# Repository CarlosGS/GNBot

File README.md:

GNBot: robotic platform for cooperative search strategies
=====

Low-cost 3D-printable robot design for testing cooperative search algorithms.  

**Check [the GNBot wiki page](https://github.com/carlosgs/GNBot/wiki) for more information**  

The GNBot design allows the construction of a swarm of remotely-controlled robots that have multimodal sensory input (perceiving light, distance, temperature, humidity and orientation with an electronic compass) and are capable of detecting odor sources such as the low-profile target shown on the left.  

**Demonstration video of the swarm of GNBots used for Lévy-walk-based search:**

These robots are also energy efficient, open-source and easy to expand to allow the implementation of a great variety of cooperative search strategies (including those that use range information from each sensor modality with a characterization of the uncertainty of odor sources, and also the ones that use classical heuristic or brute-force approaches for search). Most importantly, the standardization of the platform could finally provide a fair base of comparison for evaluating differences in efficiency among these odor search strategies.  

List of sensors present in the robot:
TGS-2600 odor sensor, IR rangefinder, LDR light sensor array, electronic compass module, temperature and humidity sensors.
Battery voltage is also monitored.
The base actuators are two servomotors and the wireless interface is based on a ZigBee-compatible module.  

**Version 1.0:**  

Items shown in the picture:
**1)** GNBoard electronics.
**2)** Arduino MEGA board.
**3)** TGS-2600 odor sensor.
**4)** ZigBee-compatible RF module.
**5)** Infra-red distance sensor.
**6)** DHT11 temperature and humidity sensor.
**7)** HMC5883L magnetometer sensor.
**8)** Piezoelectric buzzer.
**9)** Visual marker attachment.
**10)** Two 9V battery connectors.
**11)** Two 9V rechargeable batteries (300mAh).
**12)** Two continuous-rotation servomotors.
**13)** 3D-printed robot wheels.
**14)** Rubber outer-wheel rings.
**15)** 3D-printed GNBot chassis.
**16)** Marble for the idler wheel.  

**Version 1.0a:**  

**Version 0.5:**  

License  
--
License: **Attribution - Share Alike - Creative Commons (<http://creativecommons.org/licenses/by-sa/3.0/>)**  

Author:  
--
**@CarlosGS** <https://github.com/CarlosGS>

Disclaimer  
--
This hardware/software is provided "as is", and you use the hardware/software at your own risk. Under nocircumstances shall any author be liable for direct, indirect, special, incidental, or consequential damages resulting from the use, misuse, or inability to use this hardware/software, even if the authors have been advised of the possibility of such damages.

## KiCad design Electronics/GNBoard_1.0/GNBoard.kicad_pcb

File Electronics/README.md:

Electronics for the GNBot
=====

GNBoard shield for the Arduino MEGA  
--

An efficient solution for powering mobile robots. The GNBoard can also incorporate a ZigBee-compatible module and many other multimodal sensors (a gas detector for odor sensing, an accelerometer/electronic compass, temperature and humidity sensors, luminosity sensors), and multiple kinds of actuators as well (servomotors, a speaker, LEDs, etc).

The two versions of the GNBoard developed for this project.
Prototype design (left) and version 1.0 (right).
The boards are designed to plug into an **Arduino MEGA**.  

The motion of the robot is achieved using two continuous rotation servomotors (**SM-S4303R**) as the main actuators. Servomotors provide a compact and low-cost solution to achieve the digital speed control needed.
The main downside of this kind of actuator is the high current demand -particularly during transient motions- which requires the use of an adequate power supply. For the GNBoard the design decision was to use a switching power supply rather than a linear regulator, provided the much higher efficiency.

**Power supply schematic and actual assembly**
**A)** and **B)** respectively show the power supplies in GNBoard v0.1 and v1.0 (final version).
The power supply of the GNBoard uses an **LM2576-5** switching regulator that is capable of delivering up to 3A, which is more than sufficient to cover the energy demand of the entire robot.
Switching power regulators also have a broad input voltage range, allowing to make better use of the full capacity of the batteries since they can be connected in series without negative effect in the performance.

**Polarization scheme for the artificial nose sensor and detail picture of the assembly:**
The mounted sensor is the **TGS-2600** gas detector from <http://www.figarosensor.com/>, but any kind of sensor with a similar polarization scheme (as shown in the left panel) could be used.

Layout and schematics  

License  
--
License: **Attribution - Share Alike - Creative Commons (<http://creativecommons.org/licenses/by-sa/3.0/>)**  

Author:  
--
**Carlosgs (<http://carlosgs.es>)**  

Disclaimer  
--
This hardware/software is provided "as is", and you use the hardware/software at your own risk. Under nocircumstances shall any author be liable for direct, indirect, special, incidental, or consequential damages resulting from the use, misuse, or inability to use this hardware/software, even if the authors have been advised of the possibility of such damages.

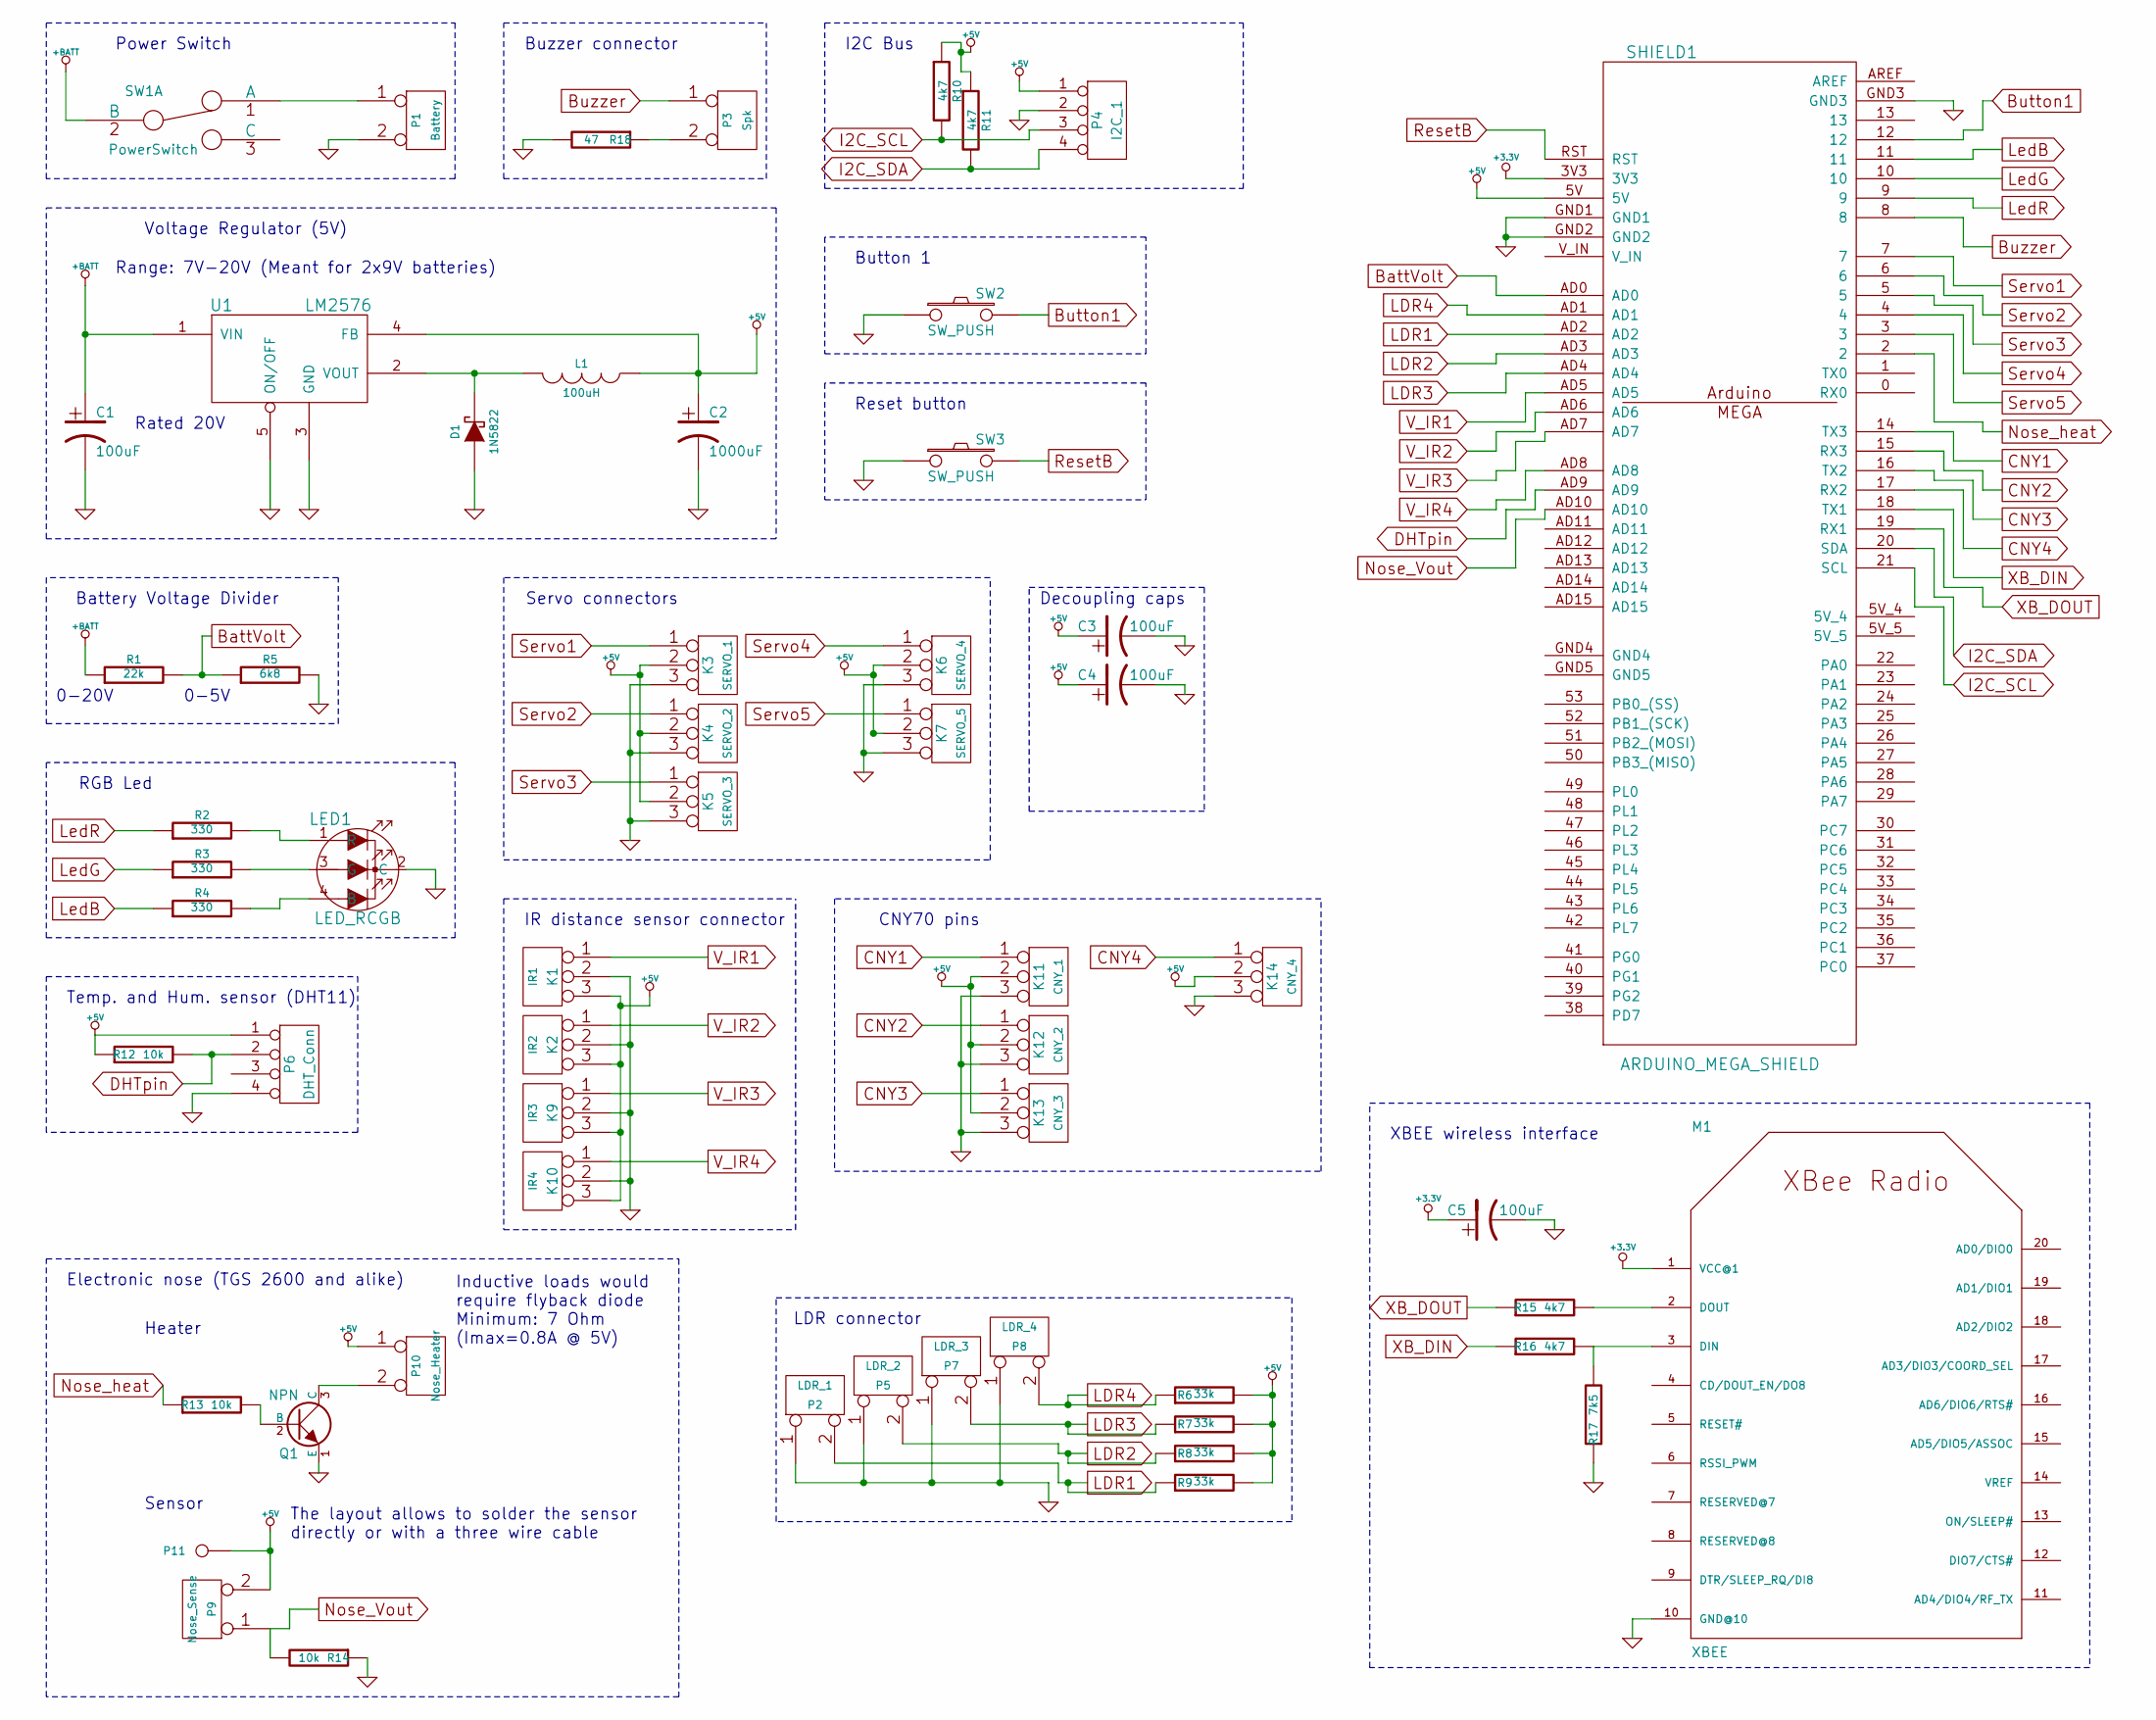
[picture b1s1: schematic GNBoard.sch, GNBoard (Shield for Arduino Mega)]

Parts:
C1, C3, C4, C5: 100uF
C2: 1000uF
D1: 1N5822
K1: IR1
K2: IR2
K3: SERVO_1
K4: SERVO_2
K5: SERVO_3
K6: SERVO_4
K7: SERVO_5
K9: IR3
K10: IR4
K11: CNY_1
K12: CNY_2
K13: CNY_3
K14: CNY_4
L1: 100uH
LED1: LED_RCGB
M1: XBEE; xbee_r1-XBEE
P1: Battery
P2: LDR_1
P3: Spk
P4: I2C_1
P5: LDR_2
P6: DHT_Conn
P7: LDR_3
P8: LDR_4
P9: Nose_Sense
P10: Nose_Heater
P11: CONN_1
Q1: NPN
R1: 22k
R2, R3, R4: 330
R5: 6k8
R6, R7, R8, R9: 33k
R10, R11, R15, R16: 4k7
R12, R13, R14: 10k
R17: 7k5
R18: 47
SHIELD1: ARDUINO_MEGA_SHIELD
SW1: PowerSwitch
SW2, SW3: SW_PUSH
U1: LM2576

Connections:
+3.3V: C5.1, M1.1 (VCC@1), SHIELD1.3V3
+5V: C2.1, C3.1, C4.1, K1.3, K2.3, K3.2 (PM), K4.2 (PM), K5.2 (PM), K6.2 (PM), K7.2 (PM), K9.3, K10.3, K11.2 (PM), K12.2 (PM), K13.2 (PM), K14.2 (PM), L1.1, P4.1, P6.1, P9.2 (PM), P10.1, P11.1, R6.2, R7.2, R8.2, R9.2, R10.1, R11.1, R12.1, SHIELD1.5V, U1.4 (FB)
+BATT: C1.1, R1.1, SW1.2 (B), U1.1 (VIN)
BattVolt: R1.2, R5.1, SHIELD1.AD0
Button1: SHIELD1.12, SW2.2
Buzzer: P3.1, SHIELD1.8
CNY1: K11.1, SHIELD1.14 (TX3)
CNY2: K12.1, SHIELD1.15 (RX3)
CNY3: K13.1, SHIELD1.16 (TX2)
CNY4: K14.1, SHIELD1.17 (RX2)
DHTpin: P6.2, R12.2, SHIELD1.AD9
GND: C1.2, C2.2, C3.2, C4.2, C5.2, D1.1 (A), K1.2 (PM), K2.2 (PM), K3.3, K4.3, K5.3, K6.3, K7.3, K9.2 (PM), K10.2 (PM), K11.3, K12.3, K13.3, K14.3, LED1.2 (C), M1.10 (GND@10), P1.2 (PM), P2.1, P4.2, P5.1, P6.4, P7.1, P8.1, Q1.1 (E), R5.2, R14.1, R17.1, R18.2, SHIELD1.GND1, SHIELD1.GND2, SHIELD1.GND3, SW2.1, SW3.1, U1.3 (GND), U1.5 (ON/OFF)
I2C_SCL: P4.3, R10.2, SHIELD1.21 (SCL)
I2C_SDA: P4.4, R11.2, SHIELD1.20 (SDA)
LDR1: P2.2 (PM), R9.1, SHIELD1.AD2
LDR2: P5.2 (PM), R8.1, SHIELD1.AD3
LDR3: P7.2 (PM), R7.1, SHIELD1.AD4
LDR4: P8.2 (PM), R6.1, SHIELD1.AD1
LedB: R4.1, SHIELD1.11
LedG: R3.1, SHIELD1.10
LedR: R2.1, SHIELD1.9
unnamed: LED1.3 (G), R3.2
unnamed: P3.2 (PM), R18.1
unnamed: LED1.4 (B), R4.2
unnamed: LED1.1 (R), R2.2
unnamed: D1.2 (K), L1.2, U1.2 (VOUT)
unnamed: P1.1, SW1.1 (A)
unnamed: M1.3 (DIN), R16.2, R17.2
unnamed: M1.2 (DOUT), R15.2
unnamed: Q1.2 (B), R13.2
unnamed: P10.2 (PM), Q1.3 (C)
Nose_Vout: P9.1, R14.2, SHIELD1.AD10
Nose_heat: R13.1, SHIELD1.2
ResetB: SHIELD1.RST, SW3.2
Servo1: K3.1, SHIELD1.7
Servo2: K4.1, SHIELD1.6
Servo3: K5.1, SHIELD1.5
Servo4: K6.1, SHIELD1.4
Servo5: K7.1, SHIELD1.3
V_IR1: K1.1, SHIELD1.AD5
V_IR2: K2.1, SHIELD1.AD6
V_IR3: K9.1, SHIELD1.AD7
V_IR4: K10.1, SHIELD1.AD8
XB_DIN: R16.1, SHIELD1.18 (TX1)
XB_DOUT: R15.1, SHIELD1.19 (RX1)

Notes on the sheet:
Voltage Regulator (5V)
RGB Led
Battery Voltage Divider
Power Switch
LDR connector
IR distance sensor connector
Servo connectors
CNY70 pins
Buzzer connector
Reset button
I2C Bus
Button 1
Temp. and Hum. sensor (DHT11)
Decoupling caps
Range: 7V-20V (Meant for 2x9V batteries)
Rated 20V
0-5V
0-20V
Electronic nose (TGS 2600 and alike)
XBEE wireless interface
Inductive loads would require flyback diode Minimum: 7 Ohm (Imax=0.8A @ 5V)
Heater
Sensor
The layout allows to solder the sensor directly or with a three wire cable

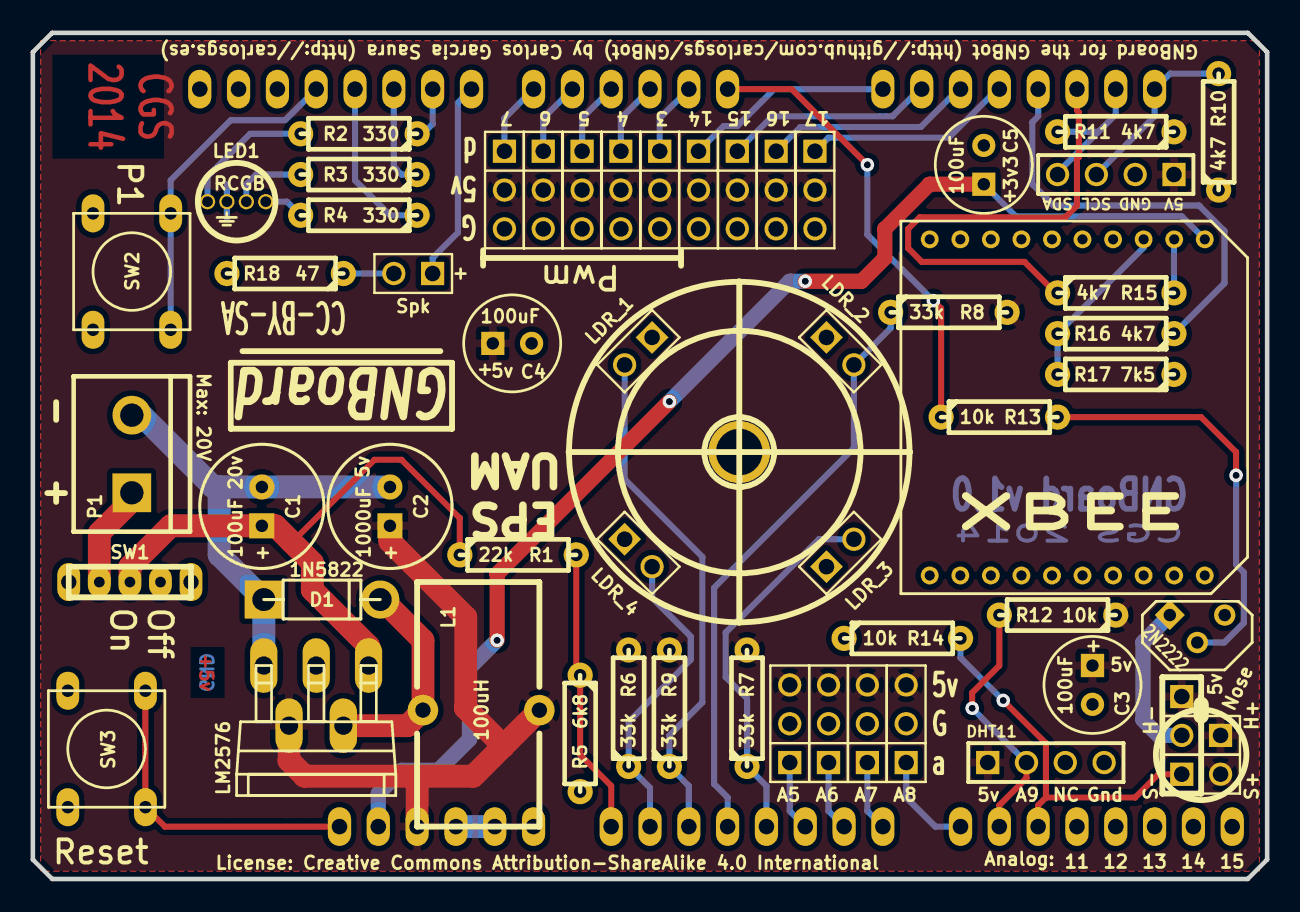
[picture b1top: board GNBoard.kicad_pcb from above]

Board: 2 copper layers, 80.8 x 55.4 mm, 58 parts (0 on the bottom side), 45 nets.

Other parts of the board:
1PIN: P***; ldr_drill

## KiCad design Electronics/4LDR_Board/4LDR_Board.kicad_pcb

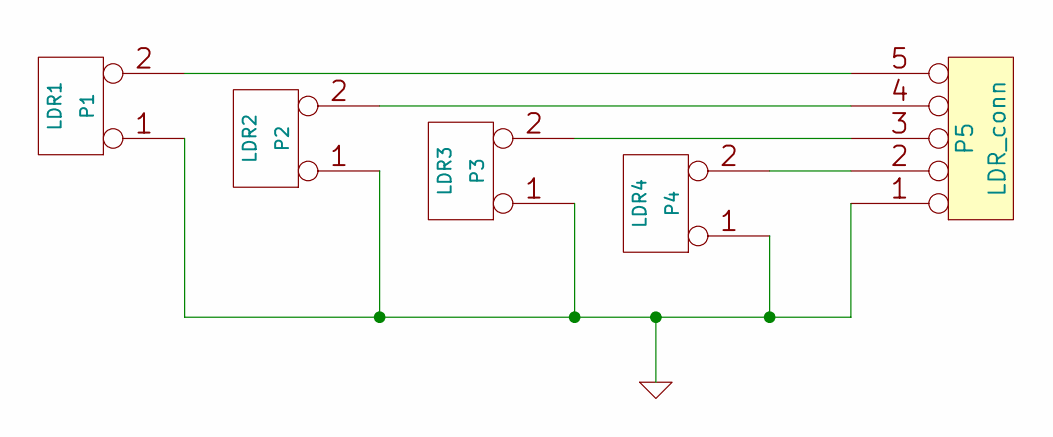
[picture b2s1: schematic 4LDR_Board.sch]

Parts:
P1: LDR1
P2: LDR2
P3: LDR3
P4: LDR4
P5: LDR_conn

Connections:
GND: P1.1, P2.1, P3.1, P4.1, P5.1
unnamed: P2.2 (PM), P5.4
unnamed: P1.2 (PM), P5.5
unnamed: P3.2 (PM), P5.3
unnamed: P4.2 (PM), P5.2

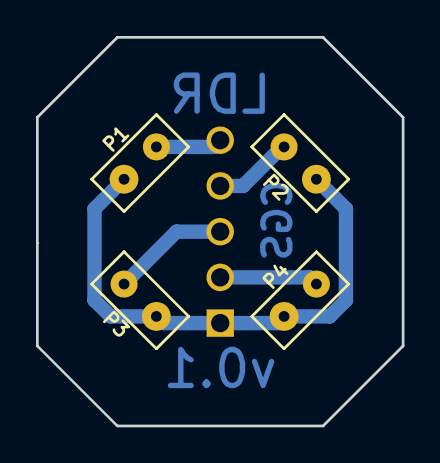
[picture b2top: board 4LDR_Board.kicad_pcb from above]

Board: 2 copper layers, 20.3 x 21.6 mm, 5 parts (1 on the bottom side), 5 nets.

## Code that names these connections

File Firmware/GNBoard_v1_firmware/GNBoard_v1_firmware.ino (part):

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
#define Serial Serial

#define NOSE_HEAT_PIN 2
#define NOSE_VOUT_PIN A10

#define LDR1_PIN A2
#define LDR2_PIN A3
#define LDR3_PIN A4
#define LDR4_PIN A1

#define IR1_PIN A5
#define IR2_PIN A6
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
#define DHT_PIN A9

#define BUZZER_PIN 8

#define SERVO_1_PIN 7
#define SERVO_2_PIN 6
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void playNote(int frequency, int length) {
  if(frequency <= 0) frequency = DO;
  if(length <= 0) length = 100;
  tone(BUZZER_PIN,frequency);
  delay(length);
  noTone(BUZZER_PIN);
  delay(100);
}

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  
  setupMagnetometer();
  
  Servo1.attach(SERVO_1_PIN);
  Servo2.attach(SERVO_2_PIN);
  Serial.begin(9600);
  
  XbeeSerial.begin(9600);
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  while(!button_is_pressed()) delay(10);
  
  int heatVal = 128;
  analogWrite(NOSE_HEAT_PIN, heatVal);
  while(1) {
    if(Serial.available()) {
      int val = Serial.read()-'0';
      if(val >= 0 && val <= 9) {
        heatVal = map(val,0,9, 0,255);
        analogWrite(NOSE_HEAT_PIN, heatVal);
      }
    }
    
    int noseV = analogRead(NOSE_VOUT_PIN);
    
    char data[128] = "";
    sprintf(data,"Heat: %d Nose: %d", heatVal, noseV);
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    Serial.print(noseV);
    
    Serial.print("\t LDR1: ");
    Serial.print(analogRead(LDR1_PIN));
    Serial.print("\t LDR2: ");
    Serial.print(analogRead(LDR2_PIN));
    Serial.print("\t LDR3: ");
    Serial.print(analogRead(LDR3_PIN));
    Serial.print("\t LDR4: ");
    Serial.print(analogRead(LDR4_PIN));
    
    Serial.print("\t Compass: ");
    Serial.print(readMagnetometer());
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      int spinVel = 10;
      //float error = angleDest-M_degrees;
      //if(abs(error) < 180.f) spinVel *= -1;
      //Servo1.write(90-spinVel);
      //Servo2.write(90-spinVel);
      
      float error = 2*margin;
      float M_degrees;
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          spinVel = spinVel/2;
        }
        
        Servo1.write(90-spinVel);
        Servo2.write(90-spinVel);
        
        delay(10);
      }
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
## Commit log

2013-06-12 Added power supply schematics
2013-06-12 Finished schematic/layout for voltage regulator, battery status meter, power switch and RGB LED.
2013-06-12 Added readme file
2013-06-12 LDR and IR connectors added to schematic
2013-06-12 Layout for the LDR
2013-06-13 v0.1 finished
2013-06-13 Added decoupling caps
2013-06-13 Finished first version, added schematics
2013-06-13 First tests, added source code
2013-06-15 Added LDR board
2013-06-16 Added manufacture process images
2013-06-16 Added Readme
2013-06-16 Added images
2013-06-16 Added comment
2013-06-17 Added caterpillar tracks
2013-06-17 Added encoder board
2013-06-17 Finished encoder board
2013-06-17 Improvements for the GNBoard
2013-06-18 Gerber export
2013-06-29 No changes
2013-08-09 Software tests and hardware concepts
2013-08-09 Added sensor input filtering
2013-08-10 Misc improvements
2013-08-10 Software telemetry tests
2013-08-11 Finished scripts, added all data + visualizations
2013-08-11 Added more PNG captures with the data not normalized
2013-08-11 Fixed issue with the representation
2013-08-14 More representation tests
2013-08-15 Robot motion script
2013-08-17 Updated the speed
2013-08-27 More tests with the light sensor
2013-10-23 GNBot misc update
2013-10-23 Code improvements, added acceleration to the firmware.
2013-10-23 Added more info and pictures
2013-10-23 Removed spaces from name of file
2013-10-24 Added a cover for the light sensor.
2013-10-25 More data with single light source
2013-10-25 Added plots for Light intensity vs Distance
2013-11-06 Design improvements, directory re-structured
2013-11-06 Hardware improvements
2013-11-07 Long range light measurements
2013-11-07 Folder renamed
2013-11-07 Removed backup files
2013-11-07 Measurements with magnetic error
2013-11-07 Updated plots with correct range of the light distance
2013-11-08 Data processed assuming linear angle measurement
2013-11-08 Added picture of the process
2013-11-13 Added linear plots with angle in degrees
2013-11-21 Moved light measurements to separate folder
2013-11-21 First steps towards robot localization
2013-11-22 Added XBee library
2013-11-22 XBee files
2014-01-14 Updated components to allow powering with up to 20V
2014-01-15 Generated PDF diagram
2014-01-21 Light model implementation
2014-01-30 Improved light model interpolation
2014-01-30 More work on the interpolation based on FFT/IFFT
2014-02-05 Working on new version. Created backup of previous design.
2014-02-06 Working in new version for the GNBoard
2014-02-06 Added support for LDRs, lots of changes
2014-02-07 Finished preliminary design
2014-02-08 Finished v1.0 of the GNBoard
2014-02-08 Updated links
2014-02-08 Moved v0.1 to its own folder
2014-02-09 Updated gerber files
2014-02-09 Resized silkscreen texts, resistor values are now shown
2014-02-10 Updated value of the resistors for the battery voltage monitor
2014-02-12 Added file
2014-02-14 Added code for the Xbees
2014-02-21 Created test for GNBoard v1
2014-02-21 Updated Readme with pictures
2014-02-23 Tested XBee support
2014-02-26 Modified LDR support to fit the new GNBoard
2014-02-26 Tests transmitting from python
2014-02-26 Improved LDR support: tuned and easier printing
2014-02-27 Updated sender/receiver addresses
2014-03-01 Tests with the nose sensor and real time plotting
2014-03-02 Calibration tests
2014-03-03 Finished implementation of light model
2014-03-03 Stored sensor fitted coeffs to file
2014-03-04 Compass and XBee comm tests
2014-03-04 Calibrated compass measurements
2014-03-05 Preliminar code for robot positioning
2014-03-05 Implemented control of the motors from python
2014-03-05 Set time scale to 20 minutes
2014-03-05 Moved data file, created backup of robotPosition.py
2014-03-05 Tested battery duration ~2h
2014-03-06 Localization tests
2014-03-07 More localization tests
2014-03-09 Implemented particle filter
2014-03-27 Battery measurements
2014-03-28 Modified representation
2014-05-20 New version of the chassis. Two 9V batteries now fit on the bottom of the robot.
2014-05-20 Merged light measurement tests
2014-05-20 Added battery holder. Some hardware tweaks for better printing
2014-05-21 Added support for frontal IR sensor
2014-05-22 Improved visualization
2014-05-22 Improved wheel tolerances
2014-05-22 Added angle to the battery holder
2014-05-23 Adjusted space for the IR distance sensor
2014-05-23 Increased space for the IR sensor
2014-07-07 Added pictures to GNBot description
2014-07-07 Added pictures to GNBoard description
2014-07-07 Added pictures to GNBot hardware description
2014-07-07 Updated description
2014-07-07 Added design files for visual markers
2014-07-07 Added 3D-printable files for visual markers and target support
2014-07-13 Added cooperative search video to README
2014-07-19 Added board layout visualizations
2014-07-19 Repository reorganization, added latest version of the GNBot platform
2014-07-19 Fixed list formatting
2014-07-19 Added LaTeX sources for the Bachelors Thesis
2014-07-19 Updated image
2014-07-27 Fixed document references
2014-08-23 Added LM14 poster PDF and ODT source
2014-08-23 Updated file
2014-09-03 Added Levy simulation
2014-09-04 Updated Levy simulators
2014-09-07 Levy vs Others evaluation
2014-09-08 Added tests with collisions
2014-09-12 Added single execution paths
2015-05-29 Added accelerometer & opencv files
2015-06-01 Implemented IMU ypr to the firmware
2015-06-01 Progress in the marker tracker
2015-06-01 Processed video
2015-06-01 Plotted the results
2015-06-01 deleted backups
2015-06-01 file mode change
2015-06-03 Added VICON reader library
2015-06-08 Added marker tracking videos, performed IR rangefinder tests
2015-06-10 Linearized IR rangefinder response
2015-06-13 work with vicon
2015-06-18 Added libs
2015-06-19 logged motor curves
2015-06-19 Logged backwards motion
2015-06-19 Added figure
2015-06-19 Added asymetric measurements
2015-06-19 Added larger diameter wheel
2015-06-20 Measured R bigger wheel
2015-07-09 Experiments on motor calibration
2015-07-13 Reduced gyro yaw drift to <0.1deg/s
2015-07-13 Removed debugging statement
2015-07-20 Finished Gyro calibration procedure
2015-07-20 Removed initial gyro stabilization delay, and worked in the PID
2015-07-21 Added min/max motor calibration
2015-07-22 Archived motor calibration tests
2015-07-22 Generated motor speed calibration data
2015-07-22 Finished motor response curve plots
2015-07-22 Linear calibration success!
2015-07-22 Calculated PWM mapping for linear trajectories
2015-07-22 Work in the plots
2015-07-23 Finished plotting motor response curves and gyro drift
2015-07-23 Renamed plot files and created robot diagram
2015-07-24 Updated diagram
2015-07-24 Finished calibrated rotation function
2015-07-25 Plotted motor calibration for robot with over-tightened wheels
2015-07-25 Implemented PID
2015-07-27 Re-arranged start-up code
2015-07-27 Calibrated linear velocities
2015-07-29 Added calibration data structure & General code cleanup
2015-07-30 Finished PID auto-tune
2015-07-30 Measured PID response
2015-07-31 Evaluated PID response vs P controller
2015-07-31 Plotted PID auto-tune process
2015-08-03 Plotted linear speed calibration
2015-08-03 Implemented linear speed calibration
2015-08-04 Speed calibration is now averaged
2015-08-04 Logging multiple IR responses
2015-08-04 Logged IR sensor calibration for multiple robots
2015-08-04 Re-fitted IR distance sensor response
2015-08-04 Fixed PID auto-tune convergence
2015-08-04 Added and tested arc functions
2015-08-06 Generated PDF & PNG
2015-08-07 Logged and processed circular motion experiment
2015-08-07 Optimized levy search simulator
2015-08-07 Logged circles for another robot
2015-08-07 Logged square trajectories at distinct speeds
2015-08-07 Processed videos
2015-08-07 Levy trials
2015-08-08 Parameter modification
2015-08-10 Adding video tracking for Wall Bounce search strategy
2015-08-10 Removed video files
2015-08-10 Added .mp4 to git ignore
2015-08-10 Processed video marker tracking for the latest experiments
2015-08-12 Added map walls to plots
2015-08-12 Post-processing of motion data, to segment each robot's trajectory
2015-08-14 Properly segmented wall bounce video footage
2015-08-14 Moved wall bounce experiments into separate old/new folders
2015-08-15 Plotted old controller vs new self-calibration
2015-08-15 Aligned time scales
2015-08-17 Improved visualization of IR rangefinder response
2015-08-19 Converted absolute symlinks to relative
2015-08-19 Finished IR sensor response plot
2015-08-19 Re-render of motor calibration plots
2015-08-19 Added dashed ydr=0 line as a reference
2015-08-20 Added 'fit' to 'v(d)'
2015-08-20 Marked the PID line as green
2015-08-20 Improved linear drift plot
2015-08-20 Finished plotting effect of friction over the linear velocity
2015-08-20 Added grid lines
2015-08-20 Added angle=0 reference line, re-arranged legend
2015-08-21 Plotted linear calib. for two different surfaces
2015-08-21 Added robot diagram as a scale reference
2015-08-21 Resized title
2015-08-22 Reduced line thickness
2015-08-23 Added line & arc distance calibration
2015-08-24 Set 1:1 scale
2015-08-24 Formatted graph
2015-08-24 Splitted robot diagrams & created one for the full calib. procedure
2015-08-25 Measured calibration times
2015-08-25 Moved diagrams to separate folder
2015-08-25 Added perspective correction diagram
2015-08-25 Added screenshots
2015-08-26 Work on the wallbounce experiment overlay
2015-08-26 Created overlay
2015-08-26 Finished figure for the experiment setup
2015-08-26 Plotted line graph
2015-08-27 Plotted linear speed calibration for two different surfaces
2015-09-01 Removed R from omega_R to avoid confusion
2015-09-01 Added text to the figure that describes the measurement of the right motor's velocity
2015-09-02 Highlighted nonlinear region
2015-09-06 Optimized figure
2015-09-11 Added mapping demo
2015-09-11 Added demo mapping png
2015-10-09 Added masters thesis
2015-10-09 Linked wiki
2015-10-09 Added LM pdf
2018-09-05 Remove obsolete website

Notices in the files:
Firmware/GNBoard_v1_firmware/GNBoard_v1_firmware.ino:
License: CC-BY-SA (http://creativecommons.org/licenses/by-sa/3.0/)
Electronics/GNBoard_1.0/GNBoard.kicad_pcb:
License: Creative Commons Attribution-ShareAlike 4.0 International
CC-BY-SA
